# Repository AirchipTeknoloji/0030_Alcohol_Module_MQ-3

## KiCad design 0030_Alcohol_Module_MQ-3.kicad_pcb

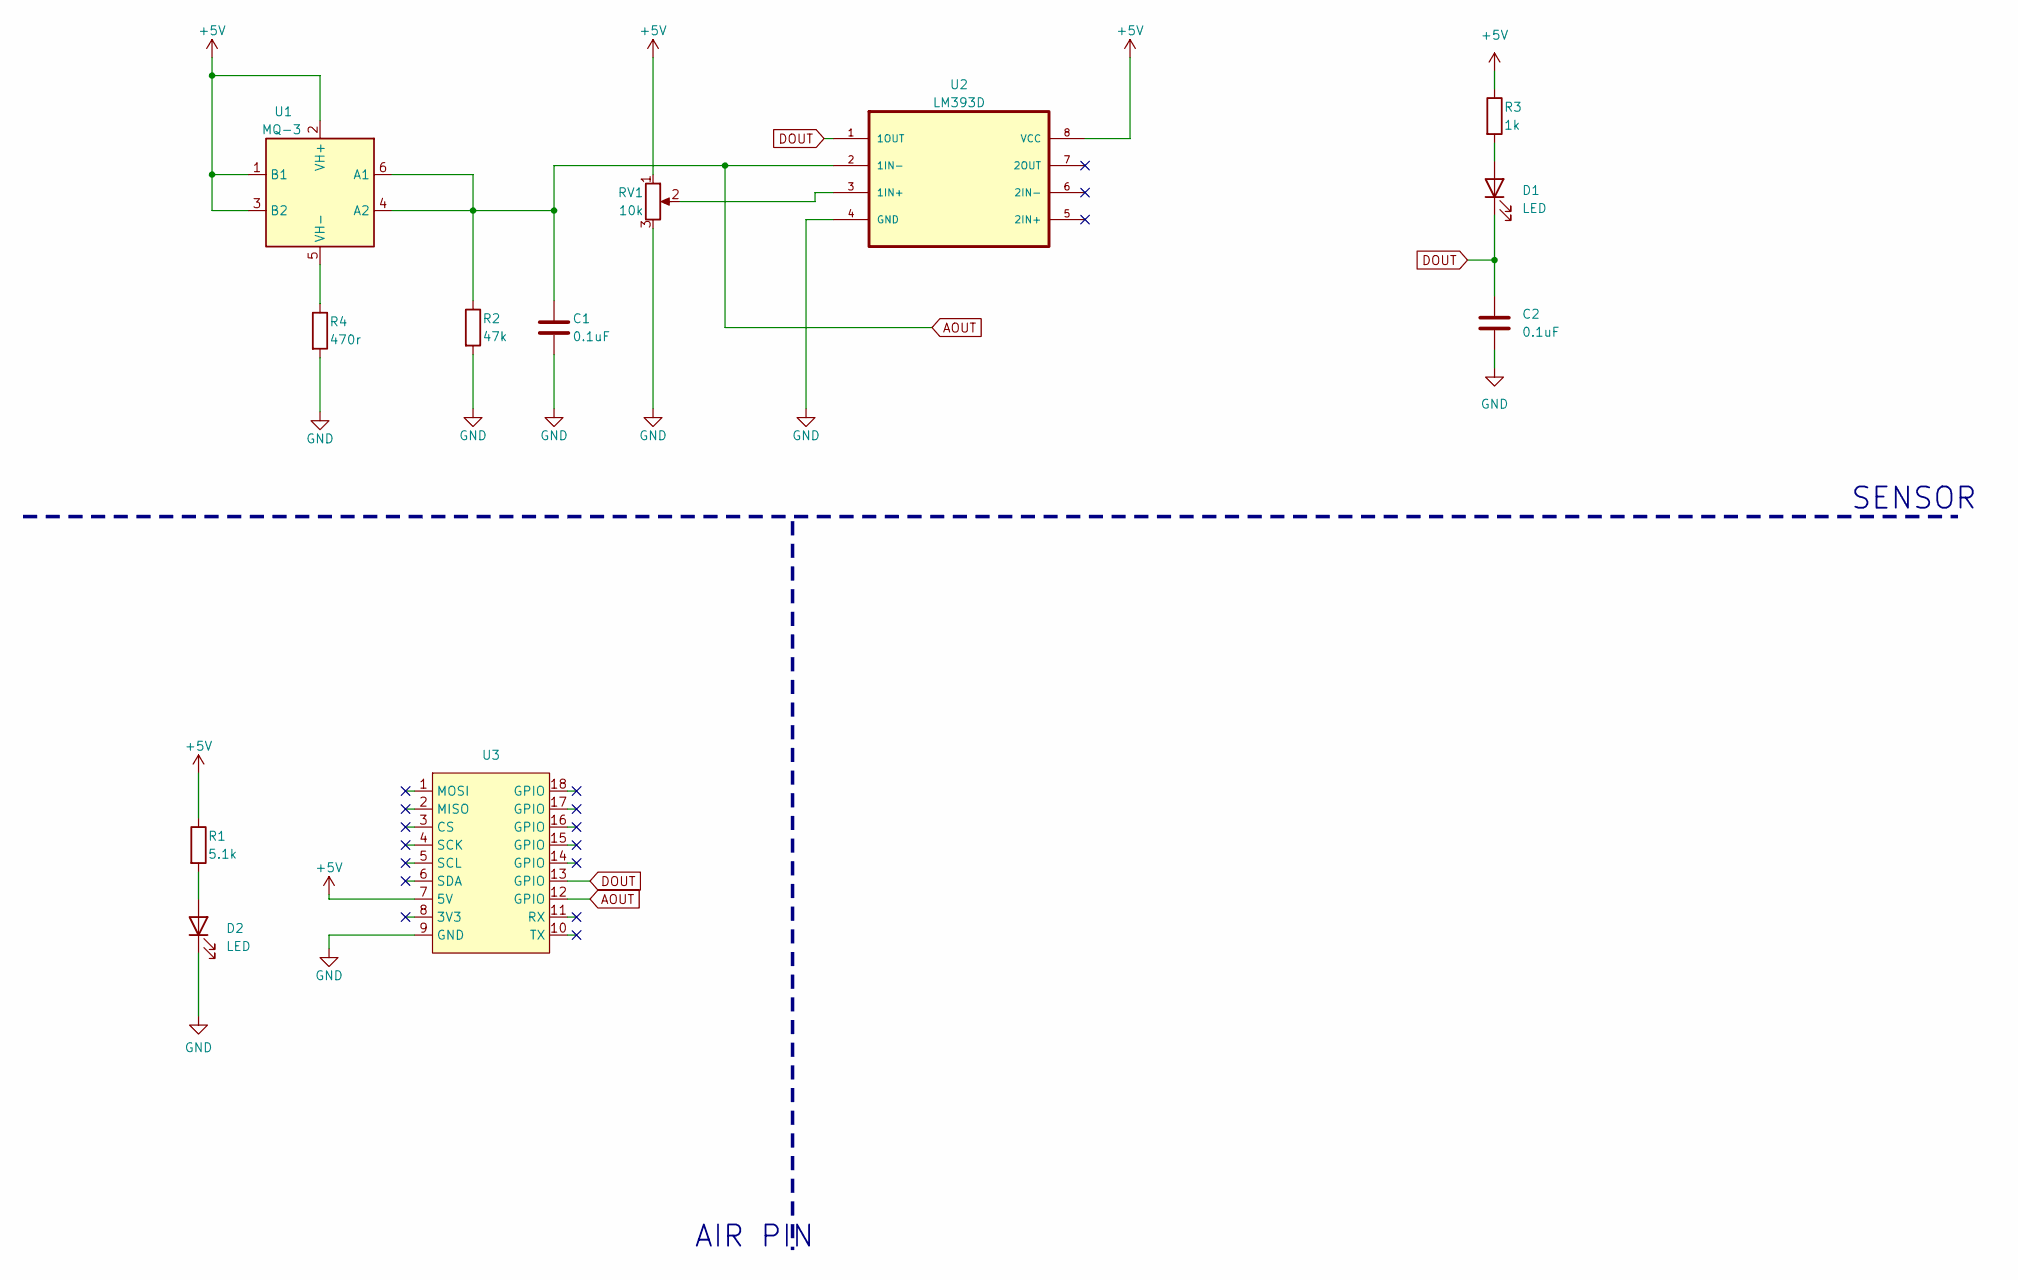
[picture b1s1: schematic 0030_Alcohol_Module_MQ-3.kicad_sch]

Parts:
C1, C2: 0.1uF; C_0805_2012Metric
D1, D2: LED; LED_0805_2012Metric
R1: 5.1k; R_0805_2012Metric
R2: 47k; R_0805_2012Metric
R3: 1k; R_0805_2012Metric
R4: 470r; R_0805_2012Metric
RV1: 10k; 3362P_1
U1: MQ-3; MQ-6
U2: LM393D; SOIC127P599X175-8N
U3: air_module

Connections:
+5V: R1.1, R3.1, U1.1 (B1), U1.2 (VH+), U1.3 (B2), U2.8 (VCC), U3.7 (5V); also elsewhere on the board
AOUT: C1.1, R2.1, U1.4 (A2), U1.6 (A1), U2.2 (1IN-), U3.12 (GPIO)
DOUT: C2.1, D1.1 (K), U2.1 (1OUT), U3.13 (GPIO)
GND: C1.2, C2.2, D2.1 (K), R2.2, R4.2, U2.4 (GND), U3.9 (GND); also elsewhere on the board
unnamed: D1.2 (A), R3.2
unnamed: D2.2 (A), R1.2
unnamed: R4.1, U1.5 (VH-)
unnamed 7: U2.3 (1IN+); also elsewhere on the board

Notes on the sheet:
AIR PIN
SENSOR

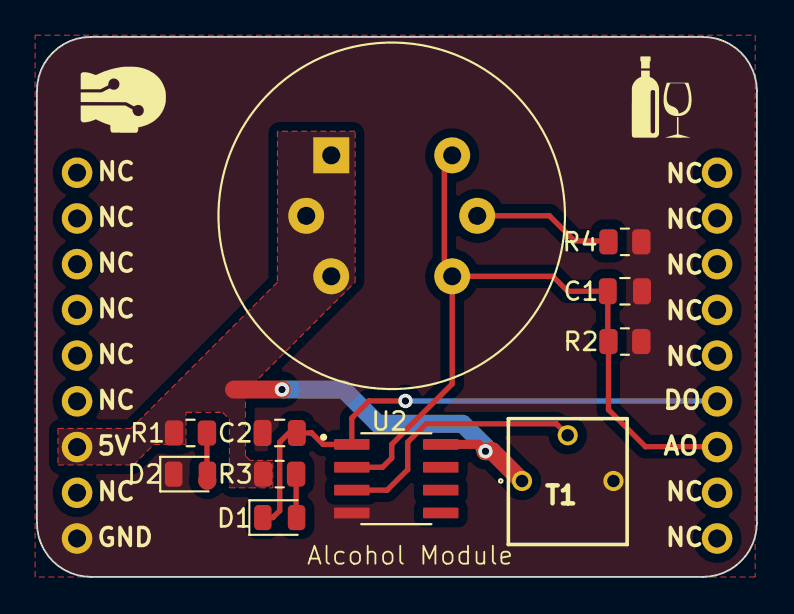
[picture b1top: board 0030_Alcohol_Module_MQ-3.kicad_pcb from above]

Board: 2 copper layers, 40.0 x 30.0 mm, 12 parts (0 on the bottom side), 8 nets.

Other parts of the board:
T1: 10k; 3362P_1

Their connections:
+5V: T1.1; also elsewhere on the board
GND: T1.3; also elsewhere on the board
unnamed 7: T1.2; also elsewhere on the board
